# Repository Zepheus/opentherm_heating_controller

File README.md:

# Andiron

**ESP32-C6 heating controller for a UK wiring centre, built for Home Assistant and ESPHome.**
Board revision v1.0

Andiron is an isolated I/O board for a domestic heating system. It sits in the
wiring centre, switches the zone valves and boiler demand through four
volt-free changeover relays, and talks to the boiler over OpenTherm. All the logic (schedules, thermostats, weather compensation) lives
in Home Assistant. The board was designed around an ESPHome firmware, which
will be written and published once the first boards are in hand.

| | |
|---|---|
| MCU | ESP32-C6-WROOM-1 (WiFi 6, BLE), USB-C power and programming |
| Boiler | OpenTherm master (opto-isolated, fused against a 230 V miswire) |
| Outputs | 4 × volt-free changeover relays (CH1–CH4), NC / COM / NO terminals, 250 VAC 3 A, each channel isolated from the others |
| Sensors | 2 × 1-Wire probe terminals (flow, outdoor), 2 × Qwiic I²C (one for the OLED, on a cable), 8-pin spare GPIO header |
| Board | 160 × 95 mm, 2 layers, wall-hanging with all cables from below or the left, 6.4 mm isolation around every relay channel, JLCPCB assembly |

> **Mains voltage.** The relay contacts can switch 230 V. Do not build or
> install it unless you are competent to work on mains wiring, and read the
> safety notes in [`docs/design.md`](docs/design.md) first. Status: v1.0 passes
> ERC, DRC and the spacing checks, but no board has been built or tested yet.

## Renders

| Top | Bottom |
|---|---|
|  |  |
|  |  |

The 3D views use stand-in models for the ESP32-C6 module (ESP32-S3-WROOM-1,
same body) and the USB-C receptacle (GCT USB4105, same footprint).

## Bill of materials

The full BOM with LCSC part numbers and cost estimates is in
[`docs/BOM.md`](docs/BOM.md); the JLCPCB upload file is
[`docs/bom/andiron-bom-jlc.csv`](docs/bom/andiron-bom-jlc.csv). At LCSC prices
from October 2026, components came to roughly $16 per board, or about $24 per
board for a run of five once Extended-part loading fees are included. The four
relays are $7.60 of that. PCB,
assembly and shipping come on top, from the JLCPCB quote.

## Getting started

### Tools

| Tool | Used for |
|---|---|
| [KiCad 10](https://www.kicad.org/) | schematic, layout, DRC, renders (`kicad-cli`) |
| [Konnect](https://github.com/mixelpixx/Konnect) MCP server (0.13, KiCad 10 plugin) | lets Claude Code read and edit the KiCad project, search the JLCPCB parts database |
| [Freerouting](https://github.com/freerouting/freerouting) 2.x + Java | autorouting |
| [easyeda2kicad](https://github.com/uPesy/easyeda2kicad.py) | importing JLC/LCSC symbols, footprints and 3D models into `lib/` |
| Python 3 | the scripts in `tools/` |

### Working on the board with Claude Code and Konnect

1. Install KiCad 10 and Konnect, and put `konnect` on your `PATH` (or point
   [`.mcp.json`](.mcp.json) at it).
2. Open the repository in Claude Code and approve the Konnect server when
   asked. Claude can then read and edit the schematic and board, run ERC and
   DRC, and search JLCPCB parts.
3. Ask Konnect to download the JLCPCB parts database once
   (`download_jlcpcb_database`); `tools/bom.py` reads the same file for prices.
4. Start with [`docs/requirements.md`](docs/requirements.md) and
   [`docs/design.md`](docs/design.md) for what the board does and why.

The layout is generated, not drawn by hand: part positions live in
`tools/layout/place.py`, shared dimensions (relay row, terminals, isolation
zones, slots, antenna keep-out) in `tools/layout/geometry.py`, and hand-laid
copper in `tools/route/prep_board.py`. Edit those and rerun the pipeline rather
than moving tracks in the PCB editor.

### Regenerating outputs

```sh
KPY=/Applications/KiCad/KiCad.app/Contents/Frameworks/Python.framework/Versions/Current/bin/python3
$KPY -I tools/sync_netlist.py "$PWD" tools/route/placed.kicad_pcb   # after a schematic change
$KPY -I tools/layout/place.py tools/route/placed.kicad_pcb          # after a placement change
tools/route/run_pipeline.sh "$PWD" 40    # route, pour, silkscreen, DRC, sanity (close the PCB editor first)
python3 tools/bom.py                     # docs/BOM.md and docs/bom/andiron-bom-jlc.csv
tools/render.sh                          # docs/images/
```

## Repository layout

| Path | What |
|---|---|
| `heating-controller.kicad_pro` / `.kicad_sch` / `.kicad_pcb` | KiCad 10 project (root sheet plus `power_mcu`, `opentherm`, `relays`) |
| `heating-controller.kicad_dru` | custom DRC rules: mains isolation, clearances, track widths |
| `.konnect/project.json` | design rules in prose, read by Konnect during layout |
| `lib/` | project symbols, footprints and 3D models (from JLC/EasyEDA) |
| `docs/requirements.md` | numbered requirements (what) |
| `docs/design.md` | decisions, safety framing, GPIO map, layout, open questions (why) |
| `docs/layout-notes.md` | what worked and what did not in placement and routing |
| `docs/BOM.md`, `docs/bom/` | bill of materials and JLCPCB upload file |
| `tools/` | routing pipeline, BOM, renders, 3D model sync, checks; see [`tools/README.md`](tools/README.md) |

Open questions that must be answered before ordering are at the end of
[`docs/design.md`](docs/design.md); the boiler model code is the main one.

## License

Open hardware. The board design and documentation are licensed under the
[CERN Open Hardware Licence v2, Permissive](LICENSES/CERN-OHL-P-2.0.txt), the
hardware counterpart of MIT; the scripts in `tools/` are under the
[MIT License](LICENSES/MIT.txt). See [`LICENSE`](LICENSE).

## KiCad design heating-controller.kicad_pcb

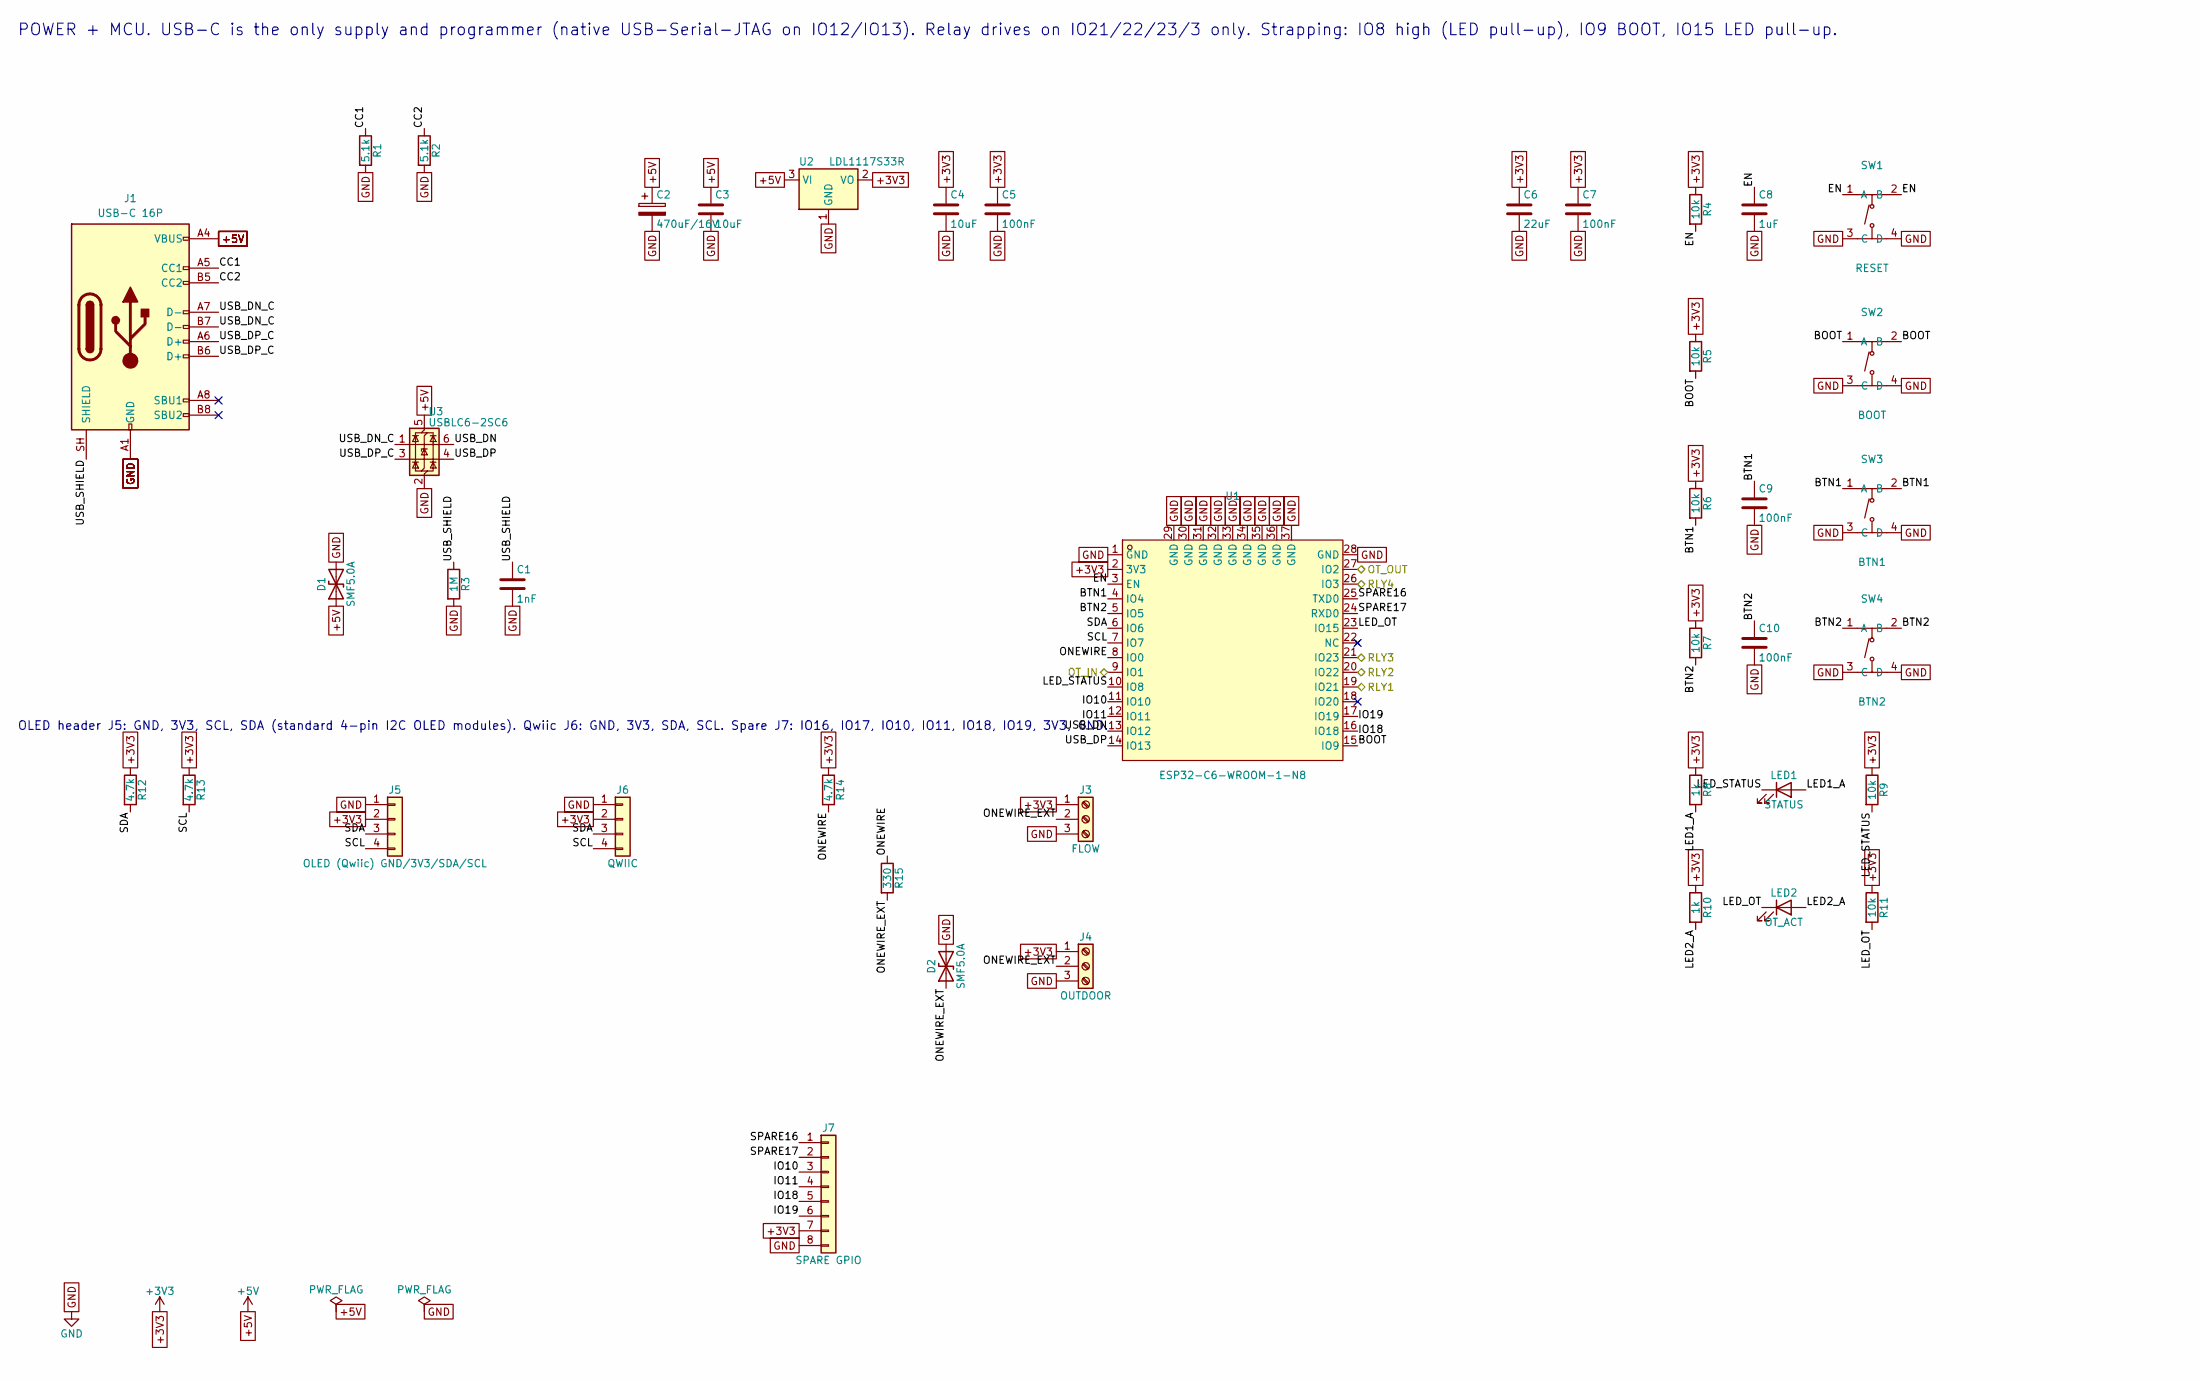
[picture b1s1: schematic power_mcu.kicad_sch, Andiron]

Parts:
C1: 1nF; C_0603_1608Metric; LCSC C1588
C2: 470uF/16V; CP_Elec_8x10; LCSC C3341
C3, C4: 10uF; C_0805_2012Metric; LCSC C15850
C5, C7, C9, C10: 100nF; C_0603_1608Metric; LCSC C14663
C6: 22uF; C_0805_2012Metric; LCSC C45783
C8: 1uF; C_0603_1608Metric; LCSC C15849
D1, D2: SMF5.0A; D_SOD-123F; LCSC C19077497
J1: USB-C 16P; USB_C_Receptacle_HRO_TYPE-C-31-M-12; LCSC C165948
J3: FLOW; CONN-TH_3P-P3.50_KF350-3.5-3P; LCSC C474893
J4: OUTDOOR; CONN-TH_3P-P3.50_KF350-3.5-3P; LCSC C474893
J5: OLED (Qwiic) GND/3V3/SDA/SCL; JST_SH_SM04B-SRSS-TB_1x04-1MP_P1.00mm_Horizontal; LCSC C160404
J6: QWIIC; JST_SH_SM04B-SRSS-TB_1x04-1MP_P1.00mm_Horizontal; LCSC C160404
J7: SPARE GPIO; PinHeader_1x08_P2.54mm_Vertical; LCSC C492407
LED1: STATUS; LED_0603_1608Metric; LCSC C2286
LED2: OT_ACT; LED_0603_1608Metric; LCSC C2286
R1, R2: 5.1k; R_0603_1608Metric; LCSC C23186
R3: 1M; R_0603_1608Metric; LCSC C22935
R4, R5, R6, R7, R9, R11: 10k; R_0603_1608Metric; LCSC C25804
R8, R10: 1k; R_0603_1608Metric; LCSC C21190
R12, R13, R14: 4.7k; R_0603_1608Metric; LCSC C23162
R15: 330; R_0603_1608Metric; LCSC C23138
SW1: RESET; SW-SMD_4P-L5.1-W5.1-P3.70-LS6.5-TL_H1.5; LCSC C318884
SW2: BOOT; SW-SMD_4P-L5.1-W5.1-P3.70-LS6.5-TL_H1.5; LCSC C318884
SW3: BTN1; SW-SMD_4P-L5.1-W5.1-P3.70-LS6.5-TL_H1.5; LCSC C318884
SW4: BTN2; SW-SMD_4P-L5.1-W5.1-P3.70-LS6.5-TL_H1.5; LCSC C318884
U1: ESP32-C6-WROOM-1-N8; WIRELM-SMD_ESP32-C6-WROOM-1; LCSC C5366877
U2: LDL1117S33R; SOT-223-3_TabPin2; LCSC C435835
U3: USBLC6-2SC6; SOT-23-6; LCSC C7519

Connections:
+3V3: C4.1, C5.1, C6.1, C7.1, J3.1, J4.1, J5.2, J6.2, J7.7, R4.1, R5.1, R6.1, R7.1, R8.1, R9.1, R10.1, R11.1, R12.1, R13.1, R14.1, U1.2 (3V3), U2.2 (VO); also elsewhere on the board
/OT_IN: U1.9 (IO1); also elsewhere on the board
/OT_OUT: U1.27 (IO2); also elsewhere on the board
/Power + MCU/BOOT: R5.2, SW2.1 (A), SW2.2 (B), U1.15 (IO9)
/Power + MCU/BTN1: C9.1, R6.2, SW3.1 (A), SW3.2 (B), U1.4 (IO4)
/Power + MCU/BTN2: C10.1, R7.2, SW4.1 (A), SW4.2 (B), U1.5 (IO5)
/Power + MCU/CC1: J1.A5 (CC1), R1.1
/Power + MCU/CC2: J1.B5 (CC2), R2.1
/Power + MCU/EN: C8.1, R4.2, SW1.1 (A), SW1.2 (B), U1.3 (EN)
/Power + MCU/IO10: J7.3, U1.11 (IO10)
/Power + MCU/IO11: J7.4, U1.12 (IO11)
/Power + MCU/IO18: J7.5, U1.16 (IO18)
/Power + MCU/IO19: J7.6, U1.17 (IO19)
/Power + MCU/LED1_A: LED1.2 (A), R8.2
/Power + MCU/LED2_A: LED2.2 (A), R10.2
/Power + MCU/LED_OT: LED2.1 (K), R11.2, U1.23 (IO15)
/Power + MCU/LED_STATUS: LED1.1 (K), R9.2, U1.10 (IO8)
/Power + MCU/ONEWIRE: R14.2, R15.1, U1.8 (IO0)
/Power + MCU/ONEWIRE_EXT: D2.1 (A1), J3.2, J4.2, R15.2
/Power + MCU/SCL: J5.4, J6.4, R13.2, U1.7 (IO7)
/Power + MCU/SDA: J5.3, J6.3, R12.2, U1.6 (IO6)
/Power + MCU/SPARE16: J7.1, U1.25 (TXD0)
/Power + MCU/SPARE17: J7.2, U1.24 (RXD0)
/Power + MCU/USB_DN: U1.13 (IO12), U3.6 (I/O1)
/Power + MCU/USB_DN_C: J1.A7 (D-), J1.B7 (D-), U3.1 (I/O1)
/Power + MCU/USB_DP: U1.14 (IO13), U3.4 (I/O2)
/Power + MCU/USB_DP_C: J1.A6 (D+), J1.B6 (D+), U3.3 (I/O2)
/Power + MCU/USB_SHIELD: C1.1, J1.SH (SHIELD), R3.1
/RLY1: U1.19 (IO21); also elsewhere on the board
/RLY2: U1.20 (IO22); also elsewhere on the board
/RLY3: U1.21 (IO23); also elsewhere on the board
/RLY4: U1.26 (IO3); also elsewhere on the board

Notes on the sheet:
POWER + MCU. USB-C is the only supply and programmer (native USB-Serial-JTAG on IO12/IO13). Relay drives on IO21/22/23/3 only. Strapping: IO8 high (LED pull-up), IO9 BOOT, IO15 LED pull-up.
OLED header J5: GND, 3V3, SCL, SDA (standard 4-pin I2C OLED modules). Qwiic J6: GND, 3V3, SDA, SCL. Spare J7: IO16, IO17, IO10, IO11, IO18, IO19, 3V3, GND.

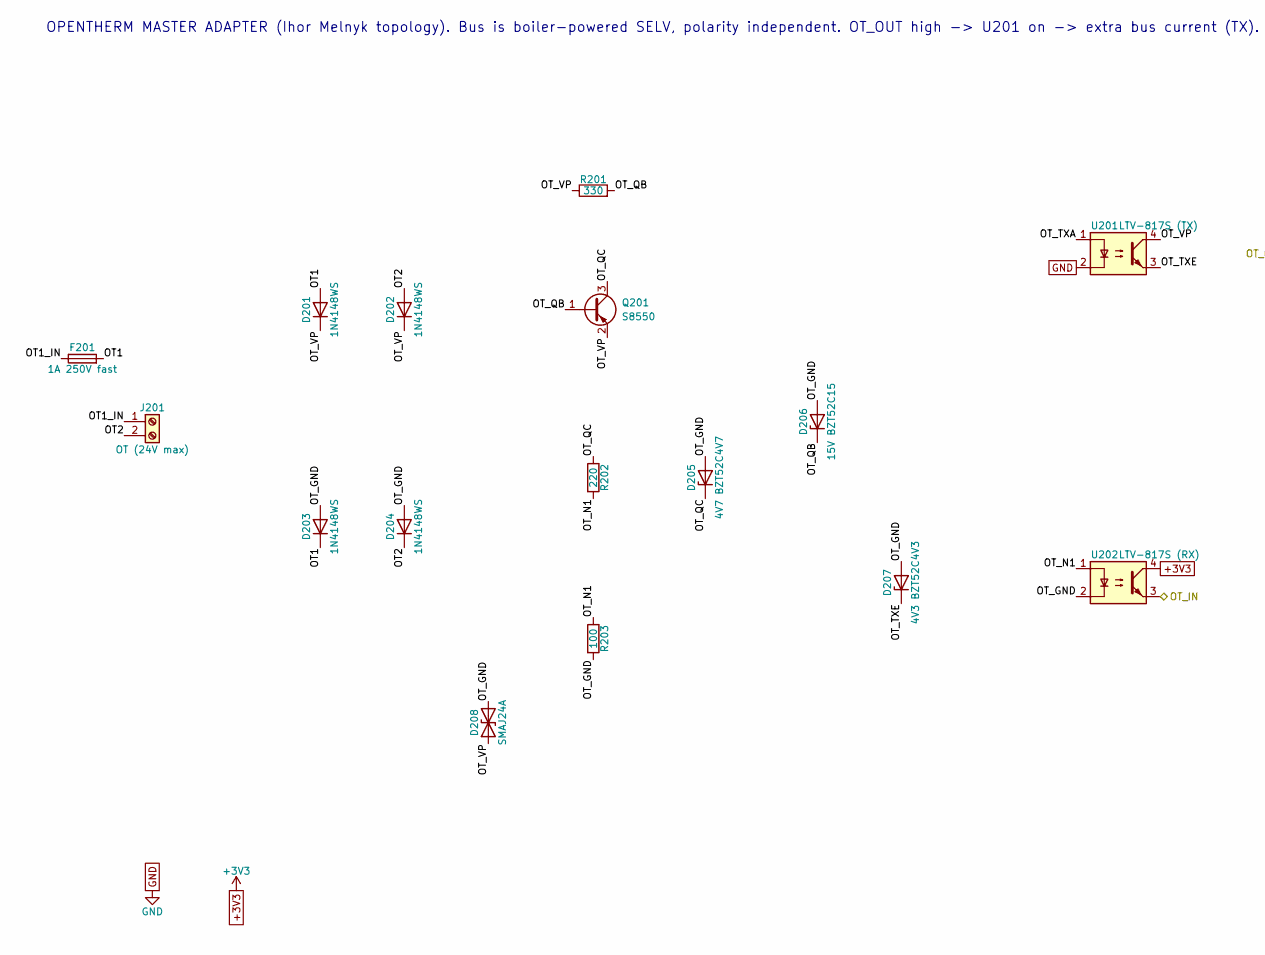
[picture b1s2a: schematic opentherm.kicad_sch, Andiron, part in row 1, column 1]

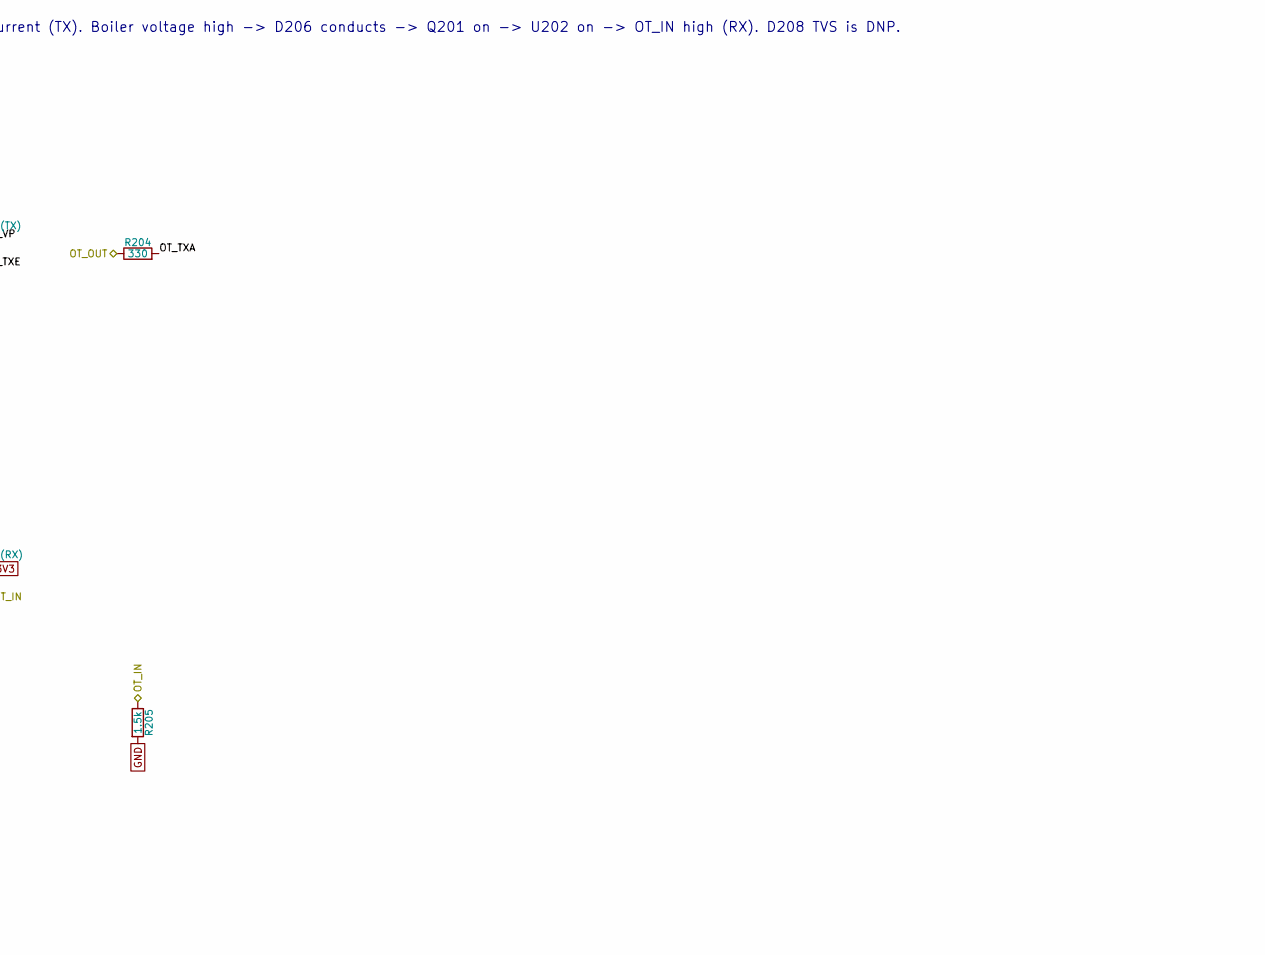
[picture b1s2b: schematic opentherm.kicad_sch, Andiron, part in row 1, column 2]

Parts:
D201, D202, D203, D204: 1N4148WS; D_SOD-323; LCSC C2128
D205: 4V7 BZT52C4V7; D_SOD-123; LCSC C19077400
D206: 15V BZT52C15; D_SOD-123; LCSC C19077412
D207: 4V3 BZT52C4V3; D_SOD-123; LCSC C19077399
D208: SMAJ24A; D_SMA; LCSC C19077541
F201: 1A 250V fast; Fuse_Littelfuse-NANO2-451_453; LCSC C83798
J201: OT (24V max); CONN-TH_P3.50_KF350-3.5-2P; LCSC C474892
Q201: S8550; SOT-23; LCSC C105432
R201: 330; R_1206_3216Metric; LCSC C17930
R202: 220; R_0603_1608Metric; LCSC C22962
R203: 100; R_0603_1608Metric; LCSC C22775
R204: 330; R_0603_1608Metric; LCSC C23138
R205: 1.5k; R_0603_1608Metric; LCSC C22843
U201: LTV-817S (TX); OPTO-SMD-4_L4.6-W6.5-P2.54-LS10.3-BL; LCSC C109227
U202: LTV-817S (RX); OPTO-SMD-4_L4.6-W6.5-P2.54-LS10.3-BL; LCSC C109227

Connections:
+3V3: U202.4; also elsewhere on the board
/OT_IN: R205.1, U202.3; also elsewhere on the board
/OT_OUT: R204.1; also elsewhere on the board
/OpenTherm/OT1: D201.2 (A), D203.1 (K), F201.2
/OpenTherm/OT1_IN: F201.1, J201.1
/OpenTherm/OT2: D202.2 (A), D204.1 (K), J201.2
/OpenTherm/OT_GND: D203.2 (A), D204.2 (A), D205.2 (A), D206.2 (A), D207.2 (A), D208.2 (A2), R203.2, U202.2
/OpenTherm/OT_N1: R202.2, R203.1, U202.1
/OpenTherm/OT_QB: D206.1 (K), Q201.1 (B), R201.2
/OpenTherm/OT_QC: D205.1 (K), Q201.3 (C), R202.1
/OpenTherm/OT_TXA: R204.2, U201.1
/OpenTherm/OT_TXE: D207.1 (K), U201.3
/OpenTherm/OT_VP: D201.1 (K), D202.1 (K), D208.1 (A1), Q201.2 (E), R201.1, U201.4

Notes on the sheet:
OPENTHERM MASTER ADAPTER (Ihor Melnyk topology). Bus is boiler-powered SELV, polarity independent. OT_OUT high -> U201 on -> extra bus current (TX). Boiler voltage high -> D206 conducts -> Q201 on -> U202 on -> OT_IN high (RX). D208 TVS is DNP.

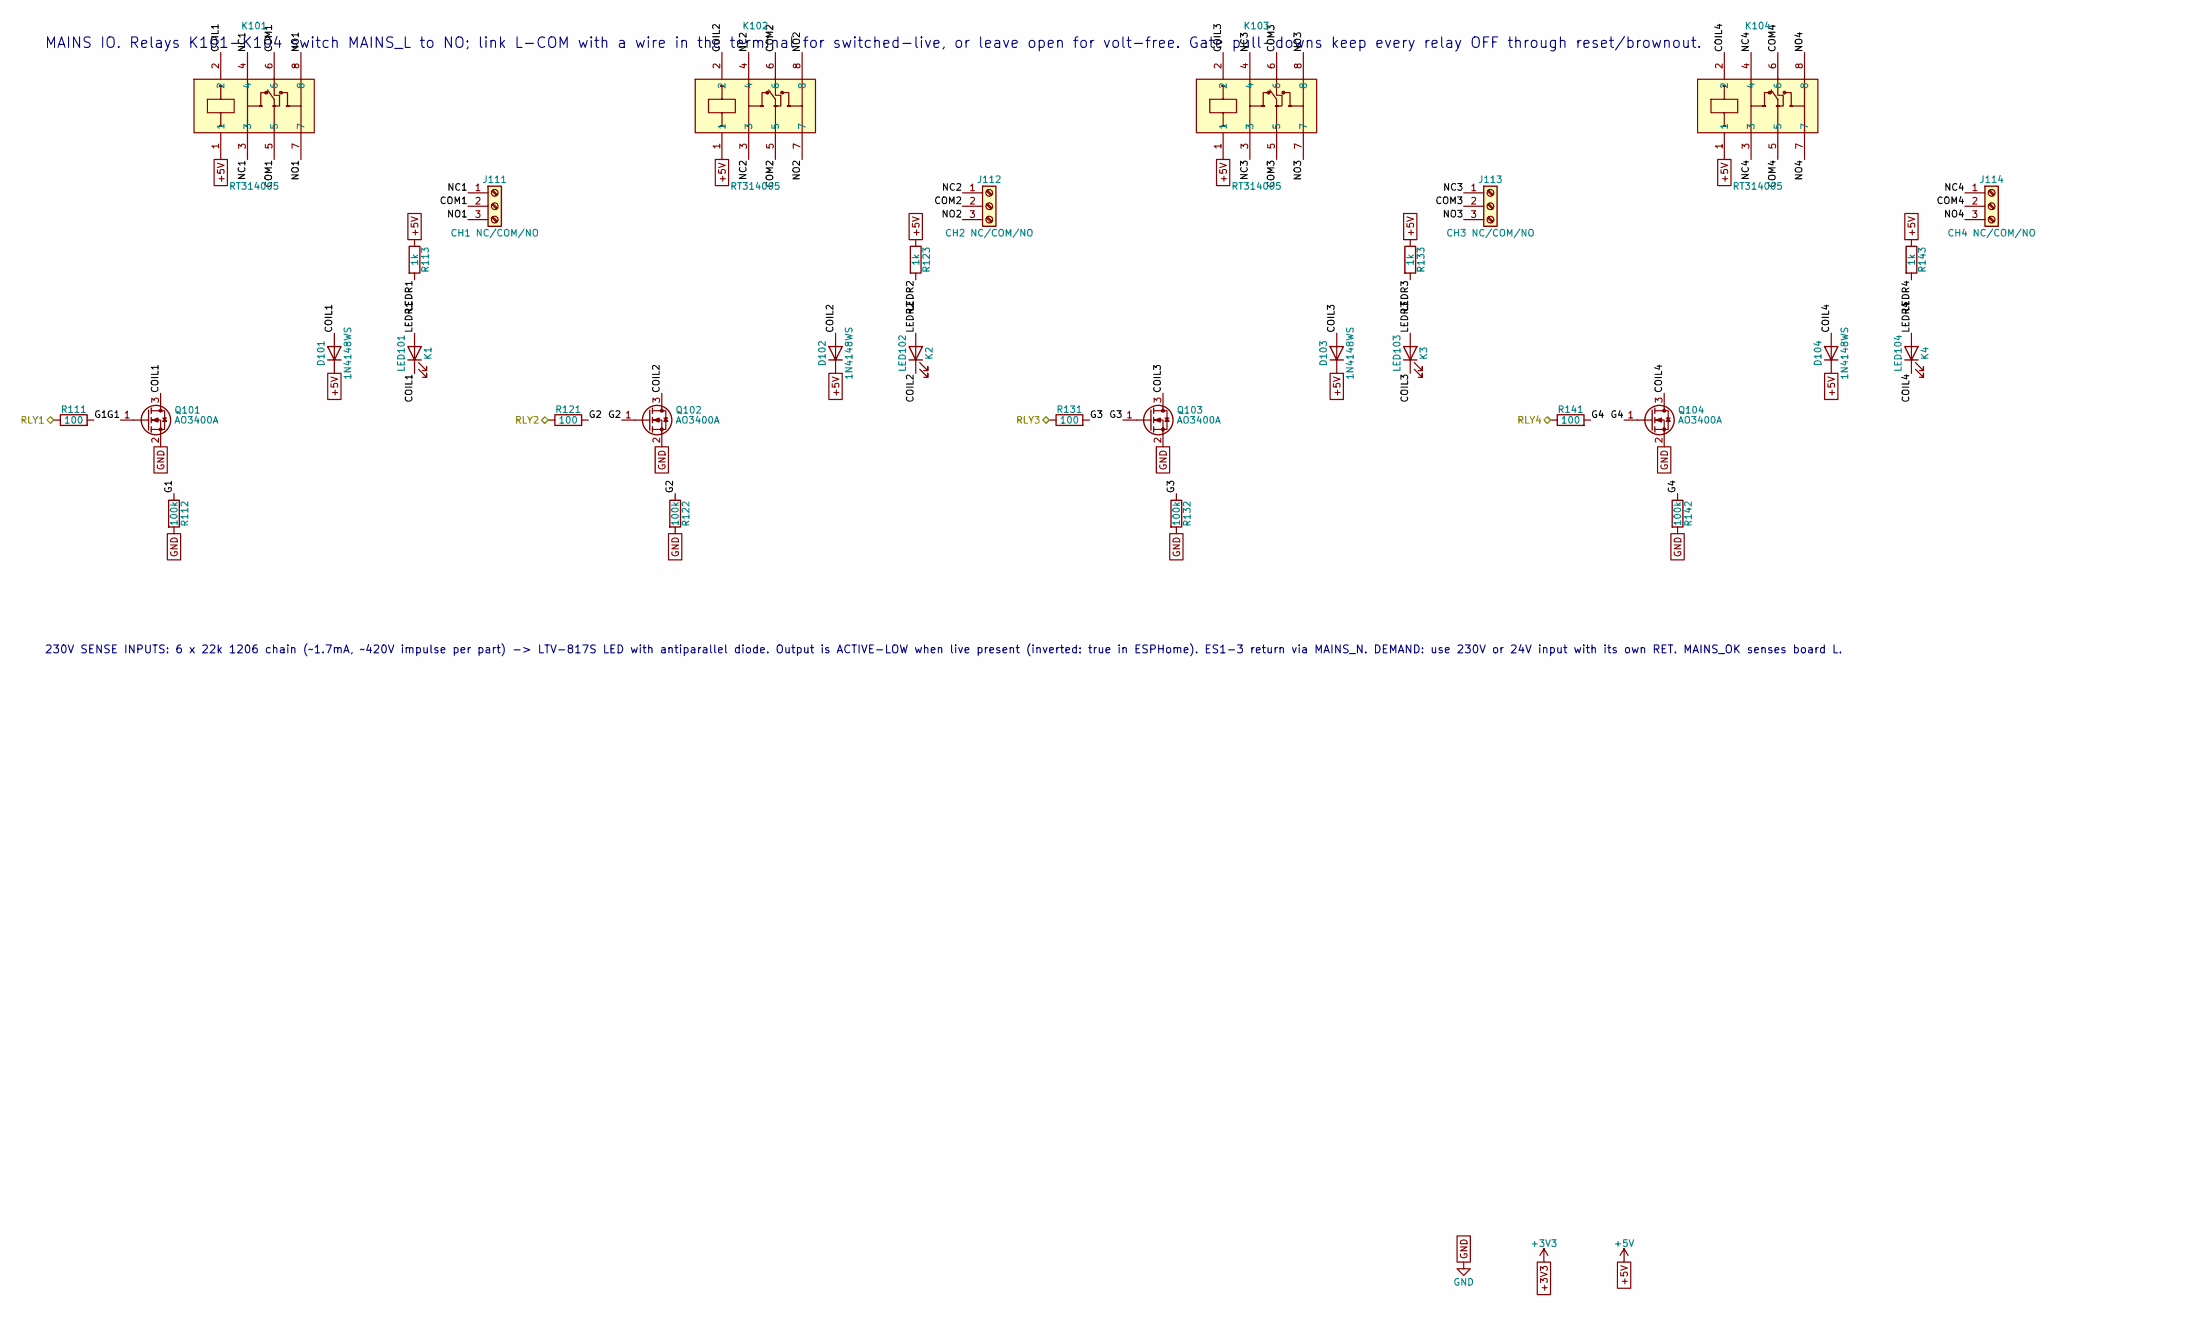
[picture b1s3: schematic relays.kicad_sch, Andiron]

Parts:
D101, D102, D103, D104: 1N4148WS; D_SOD-323; LCSC C2128
J111: CH1 NC/COM/NO; CONN-TH_3P-P5.00_WJ128V-5.0-3P; LCSC C8270
J112: CH2 NC/COM/NO; CONN-TH_3P-P5.00_WJ128V-5.0-3P; LCSC C8270
J113: CH3 NC/COM/NO; CONN-TH_3P-P5.00_WJ128V-5.0-3P; LCSC C8270
J114: CH4 NC/COM/NO; CONN-TH_3P-P5.00_WJ128V-5.0-3P; LCSC C8270
K101, K102, K103, K104: RT314005; RELAY-TH_RT314005_HF115F-PINS; LCSC C7065270
LED101: K1; LED_0603_1608Metric; LCSC C2286
LED102: K2; LED_0603_1608Metric; LCSC C2286
LED103: K3; LED_0603_1608Metric; LCSC C2286
LED104: K4; LED_0603_1608Metric; LCSC C2286
Q101, Q102, Q103, Q104: AO3400A; SOT-23; LCSC C20917
R111, R121, R131, R141: 100; R_0603_1608Metric; LCSC C22775
R112, R122, R132, R142: 100k; R_0603_1608Metric; LCSC C25803
R113, R123, R133, R143: 1k; R_0603_1608Metric; LCSC C21190

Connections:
/RLY1: R111.1; also elsewhere on the board
/RLY2: R121.1; also elsewhere on the board
/RLY3: R131.1; also elsewhere on the board
/RLY4: R141.1; also elsewhere on the board
/Relays/COIL1: D101.2 (A), K101.2, LED101.1 (K), Q101.3 (D)
/Relays/COIL2: D102.2 (A), K102.2, LED102.1 (K), Q102.3 (D)
/Relays/COIL3: D103.2 (A), K103.2, LED103.1 (K), Q103.3 (D)
/Relays/COIL4: D104.2 (A), K104.2, LED104.1 (K), Q104.3 (D)
/Relays/COM1: J111.2, K101.5, K101.6
/Relays/COM2: J112.2, K102.5, K102.6
/Relays/COM3: J113.2, K103.5, K103.6
/Relays/COM4: J114.2, K104.5, K104.6
/Relays/G1: Q101.1 (G), R111.2, R112.1
/Relays/G2: Q102.1 (G), R121.2, R122.1
/Relays/G3: Q103.1 (G), R131.2, R132.1
/Relays/G4: Q104.1 (G), R141.2, R142.1
/Relays/LEDR1: LED101.2 (A), R113.2
/Relays/LEDR2: LED102.2 (A), R123.2
/Relays/LEDR3: LED103.2 (A), R133.2
/Relays/LEDR4: LED104.2 (A), R143.2
/Relays/NC1: J111.1, K101.3, K101.4
/Relays/NC2: J112.1, K102.3, K102.4
/Relays/NC3: J113.1, K103.3, K103.4
/Relays/NC4: J114.1, K104.3, K104.4
/Relays/NO1: J111.3, K101.7, K101.8
/Relays/NO2: J112.3, K102.7, K102.8
/Relays/NO3: J113.3, K103.7, K103.8
/Relays/NO4: J114.3, K104.7, K104.8

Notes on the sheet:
MAINS IO. Relays K101-K104 switch MAINS_L to NO; link L-COM with a wire in the terminal for switched-live, or leave open for volt-free. Gate pull-downs keep every relay OFF through reset/brownout.
230V SENSE INPUTS: 6 x 22k 1206 chain (~1.7mA, ~420V impulse per part) -> LTV-817S LED with antiparallel diode. Output is ACTIVE-LOW when live present (inverted: true in ESPHome). ES1-3 return via MAINS_N. DEMAND: use 230V or 24V input with its own RET. MAINS_OK senses board L.

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
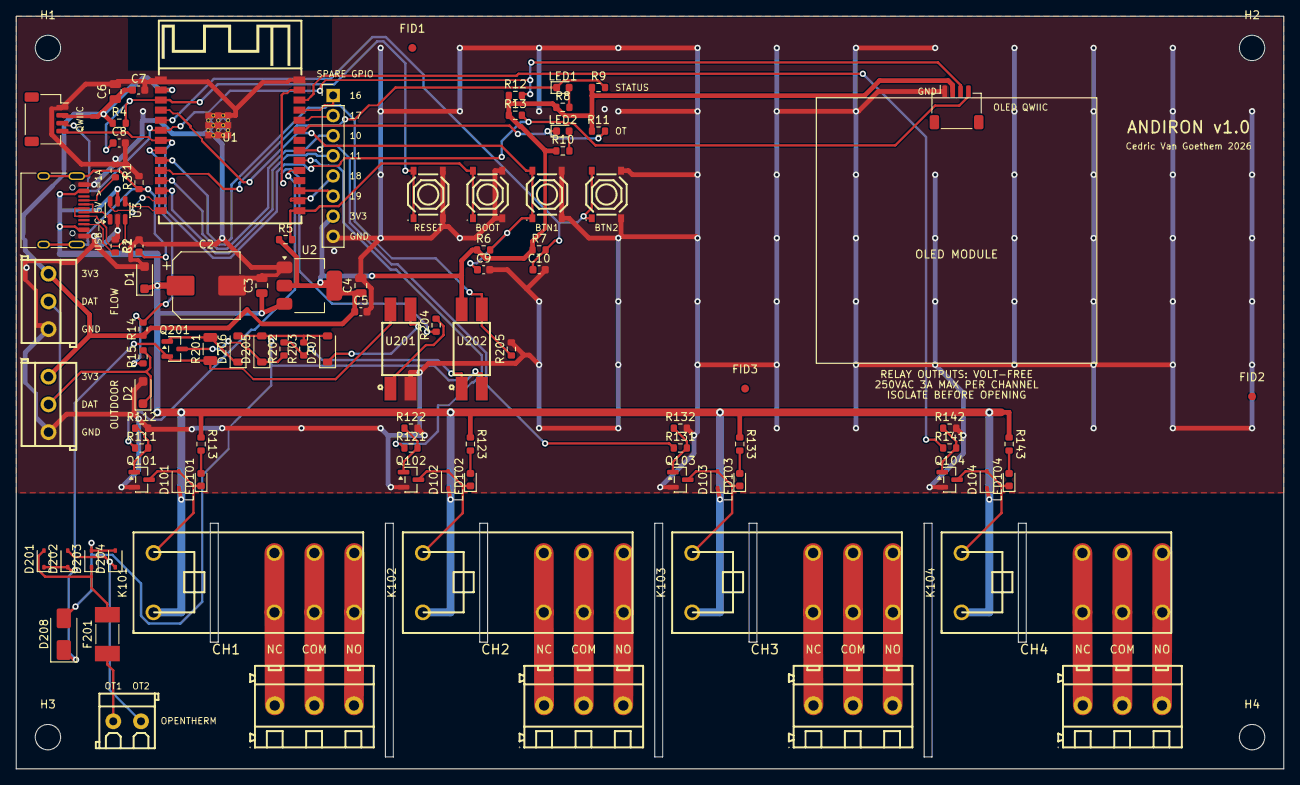
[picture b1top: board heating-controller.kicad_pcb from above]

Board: 2 copper layers, 160.0 x 95.0 mm, 99 parts (0 on the bottom side), 68 nets.

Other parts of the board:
FID1, FID2, FID3: Fiducial_1mm_Mask3mm
H1, H2, H3, H4: MountingHole_3.2mm_M3

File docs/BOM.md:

# Andiron v1.0 — bill of materials

Generated by `tools/bom.py` from the schematic on 2026-10-22. Prices: LCSC single-unit prices from the JLCPCB parts database snapshot of 2026-10-20; they are estimates, not a quote. Upload file for JLCPCB assembly: [`bom/andiron-bom-jlc.csv`](bom/andiron-bom-jlc.csv) (fitted parts only; the placement file comes from the board).

## Cost summary

| Item | USD |
|---|---:|
| Components per board (92 placements, 39 unique parts) | 15.96 |
| Extended-part loading fees per order (13 × $3.00, assumed) | 39.00 |
| **Components per board at 5 boards, fees included** | **23.76** |

PCB fabrication, assembly setup, through-hole soldering, stencil and shipping are not included; take them from the JLCPCB quote. The Library column is what the parts database reports; "Preferred" parts carry no loading fee on Economic assembly, so only "Extended" parts are counted. Swapping an Extended part for a Basic or Preferred equivalent saves its fee.

## Fitted parts

| Qty | References | Value | Footprint | LCSC | Manufacturer part | Library | Unit | Line |
|---:|---|---|---|---|---|---|---:|---:|
| 1 | C1 | 1nF | C_0603_1608Metric | [C1588](https://jlcpcb.com/partdetail/C1588) | Samsung Electro-Mechanics CL10B102KB8NNNC | Basic | 0.0090 | 0.01 |
| 1 | C2 | 470uF/16V | CP_Elec_8x10 | [C3341](https://jlcpcb.com/partdetail/C3341) | Honor Elec RVT1C471M0810 | Extended | 0.0650 | 0.07 |
| 2 | C3, C4 | 10uF | C_0805_2012Metric | [C15850](https://jlcpcb.com/partdetail/C15850) | Samsung Electro-Mechanics CL21A106KAYNNNE | Basic | 0.0440 | 0.09 |
| 4 | C5, C7, C9, C10 | 100nF | C_0603_1608Metric | [C14663](https://jlcpcb.com/partdetail/C14663) | YAGEO CC0603KRX7R9BB104 | Basic | 0.0110 | 0.04 |
| 1 | C6 | 22uF | C_0805_2012Metric | [C45783](https://jlcpcb.com/partdetail/C45783) | Samsung Electro-Mechanics CL21A226MAQNNNE | Basic | 0.1940 | 0.19 |
| 1 | C8 | 1uF | C_0603_1608Metric | [C15849](https://jlcpcb.com/partdetail/C15849) | Samsung Electro-Mechanics CL10A105KB8NNNC | Basic | 0.0140 | 0.01 |
| 2 | D1, D2 | SMF5.0A | D_SOD-123F | [C19077497](https://jlcpcb.com/partdetail/C19077497) | hongjiacheng SMF5.0A | Preferred | 0.0280 | 0.06 |
| 8 | D101, D102, D103, D104, D201, D202, D203, D204 | 1N4148WS | D_SOD-323 | [C2128](https://jlcpcb.com/partdetail/C2128) | Jiangsu Changjing Electronics Technology Co., Ltd. 1N4148WS | Basic | 0.0150 | 0.12 |
| 1 | D205 | 4V7 BZT52C4V7 | D_SOD-123 | [C19077400](https://jlcpcb.com/partdetail/C19077400) | hongjiacheng BZT52C4V7 | Preferred | 0.0120 | 0.01 |
| 1 | D206 | 15V BZT52C15 | D_SOD-123 | [C19077412](https://jlcpcb.com/partdetail/C19077412) | hongjiacheng BZT52C15 | Preferred | 0.0180 | 0.02 |
| 1 | D207 | 4V3 BZT52C4V3 | D_SOD-123 | [C19077399](https://jlcpcb.com/partdetail/C19077399) | hongjiacheng BZT52C4V3 | Preferred | 0.0180 | 0.02 |
| 1 | D208 | SMAJ24A | D_SMA | [C19077541](https://jlcpcb.com/partdetail/C19077541) | hongjiacheng SMAJ24A | Preferred | 0.0380 | 0.04 |
| 1 | F201 | 1A 250V fast | Fuse_Littelfuse-NANO2-451_453 | [C83798](https://jlcpcb.com/partdetail/C83798) | AEM MF2410F1.000TM | Extended | 0.0930 | 0.09 |
| 1 | J1 | USB-C 16P | USB_C_Receptacle_HRO_TYPE-C-31-M-12 | [C165948](https://jlcpcb.com/partdetail/C165948) | Korean Hroparts Elec TYPE-C-31-M-12 | Extended | 0.1860 | 0.19 |
| 2 | J3, J4 | FLOW / OUTDOOR | CONN-TH_3P-P3.50_KF350-3.5-3P | [C474893](https://jlcpcb.com/partdetail/C474893) | Cixi Kefa Elec KF350-3.5-3P | Extended | 0.1550 | 0.31 |
| 2 | J5, J6 | OLED (Qwiic) GND/3V3/SDA/SCL / QWIIC | JST_SH_SM04B-SRSS-TB_1x04-1MP_P1.00mm_Horizontal | [C160404](https://jlcpcb.com/partdetail/C160404) | JST SM04B-SRSS-TB(LF)(SN) | Extended | 0.2140 | 0.43 |
| 1 | J7 | SPARE GPIO | PinHeader_1x08_P2.54mm_Vertical | [C492407](https://jlcpcb.com/partdetail/C492407) | XFCN PZ254V-11-08P | Extended | 0.0520 | 0.05 |
| 4 | J111, J112, J113, J114 | CH1 NC/COM/NO / CH2 NC/COM/NO / CH3 NC/COM/NO / CH4 NC/COM/NO | CONN-TH_3P-P5.00_WJ128V-5.0-3P | [C8270](https://jlcpcb.com/partdetail/C8270) | Ningbo Kangnex Elec WJ128V-5.0-03P-14-00A | Extended | 0.2090 | 0.84 |
| 1 | J201 | OT (24V max) | CONN-TH_P3.50_KF350-3.5-2P | [C474892](https://jlcpcb.com/partdetail/C474892) | Cixi Kefa Elec KF350-3.5-2P | Extended | 0.1190 | 0.12 |
| 4 | K101, K102, K103, K104 | RT314005 | RELAY-TH_RT314005_HF115F-PINS | [C7065270](https://jlcpcb.com/partdetail/C7065270) | TE Connectivity RT314005 | Extended | 1.8920 | 7.57 |
| 6 | LED1, LED2, LED101, LED102, LED103, LED104 | STATUS / OT_ACT / K1 / K2 / K3 / K4 | LED_0603_1608Metric | [C2286](https://jlcpcb.com/partdetail/C2286) | Hubei KENTO Elec KT-0603R | Basic | 0.0080 | 0.05 |
| 4 | Q101, Q102, Q103, Q104 | AO3400A | SOT-23 | [C20917](https://jlcpcb.com/partdetail/C20917) | Alpha & Omega Semicon AO3400A | Basic | 0.0970 | 0.39 |
| 1 | Q201 | S8550 | SOT-23 | [C105432](https://jlcpcb.com/partdetail/C105432) | Jiangsu Changjing Electronics Technology Co., Ltd. S8550(RANGE:120-200) | Basic | 0.0170 | 0.02 |
| 2 | R1, R2 | 5.1k | R_0603_1608Metric | [C23186](https://jlcpcb.com/partdetail/C23186) | UNI-ROYAL(Uniroyal Elec) 0603WAF5101T5E | Basic | 0.0020 | 0.00 |
| 1 | R3 | 1M | R_0603_1608Metric | [C22935](https://jlcpcb.com/partdetail/C22935) | UNI-ROYAL(Uniroyal Elec) 0603WAF1004T5E | Basic | 0.0020 | 0.00 |
| 6 | R4, R5, R6, R7, R9, R11 | 10k | R_0603_1608Metric | [C25804](https://jlcpcb.com/partdetail/C25804) | UNI-ROYAL(Uniroyal Elec) 0603WAF1002T5E | Basic | 0.0020 | 0.01 |
| 6 | R8, R10, R113, R123, R133, R143 | 1k | R_0603_1608Metric | [C21190](https://jlcpcb.com/partdetail/C21190) | UNI-ROYAL(Uniroyal Elec) 0603WAF1001T5E | Basic | 0.0030 | 0.02 |
| 3 | R12, R13, R14 | 4.7k | R_0603_1608Metric | [C23162](https://jlcpcb.com/partdetail/C23162) | UNI-ROYAL(Uniroyal Elec) 0603WAF4701T5E | Basic | 0.0030 | 0.01 |
| 2 | R15, R204 | 330 | R_0603_1608Metric | [C23138](https://jlcpcb.com/partdetail/C23138) | UNI-ROYAL(Uniroyal Elec) 0603WAF3300T5E | Basic | 0.0020 | 0.00 |
| 5 | R111, R121, R131, R141, R203 | 100 | R_0603_1608Metric | [C22775](https://jlcpcb.com/partdetail/C22775) | UNI-ROYAL(Uniroyal Elec) 0603WAF1000T5E | Basic | 0.0030 | 0.01 |
| 4 | R112, R122, R132, R142 | 100k | R_0603_1608Metric | [C25803](https://jlcpcb.com/partdetail/C25803) | UNI-ROYAL(Uniroyal Elec) 0603WAF1003T5E | Basic | 0.0030 | 0.01 |
| 1 | R201 | 330 | R_1206_3216Metric | [C17930](https://jlcpcb.com/partdetail/C17930) | UNI-ROYAL(Uniroyal Elec) 1206W4F3300T5E | Extended | 0.0050 | 0.01 |
| 1 | R202 | 220 | R_0603_1608Metric | [C22962](https://jlcpcb.com/partdetail/C22962) | UNI-ROYAL(Uniroyal Elec) 0603WAF2200T5E | Basic | 0.0030 | 0.00 |
| 1 | R205 | 1.5k | R_0603_1608Metric | [C22843](https://jlcpcb.com/partdetail/C22843) | UNI-ROYAL(Uniroyal Elec) 0603WAF1501T5E | Basic | 0.0020 | 0.00 |
| 4 | SW1, SW2, SW3, SW4 | RESET / BOOT / BTN1 / BTN2 | SW-SMD_4P-L5.1-W5.1-P3.70-LS6.5-TL_H1.5 | [C318884](https://jlcpcb.com/partdetail/C318884) | XKB Connection TS-1187A-B-A-B | Basic | 0.0210 | 0.08 |
| 1 | U1 | ESP32-C6-WROOM-1-N8 | WIRELM-SMD_ESP32-C6-WROOM-1 | [C5366877](https://jlcpcb.com/partdetail/C5366877) | Espressif Systems ESP32-C6-WROOM-1-N8 | Extended | 4.2330 | 4.23 |
| 1 | U2 | LDL1117S33R | SOT-223-3_TabPin2 | [C435835](https://jlcpcb.com/partdetail/C435835) | STMicroelectronics LDL1117S33R | Extended | 0.5010 | 0.50 |
| 1 | U3 | USBLC6-2SC6 | SOT-23-6 | [C7519](https://jlcpcb.com/partdetail/C7519) | STMicroelectronics USBLC6-2SC6 | Extended | 0.1770 | 0.18 |
| 2 | U201, U202 | LTV-817S (TX) / LTV-817S (RX) | OPTO-SMD-4_L4.6-W6.5-P2.54-LS10.3-BL | [C109227](https://jlcpcb.com/partdetail/C109227) | Lite-On LTV-817S-TA1-C | Basic | 0.0790 | 0.16 |

## Not fitted (DNP)

| Reference | Value | Why it is on the board |
|---|---|---|

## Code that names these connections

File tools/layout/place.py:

"""Placement of the Andiron board by module area. Writes positions and the outline into tools/route/placed.kicad_pcb.

The board hangs on a wall with every field cable coming from below or from the left (geometry.py):
  bottom edge   OpenTherm terminal in the left corner, then the four relay channels: terminal on the edge with its
                entries facing out, relay above it lying on its side (coil left, NC/COM/NO right), driver above the coil
  left edge     Qwiic, USB-C, FLOW and OUTDOOR terminals, entries facing out
  top-left      ESP32-C6 module, antenna at the top edge (no cables there); its left pin column faces the left-edge
                connectors (I2C, EN, buttons, USB), its right column the spare header, BOOT, relay drives and OT_OUT
  below module  power: USB protection at the receptacle, bulk capacitor, regulator; 1-Wire parts at the probe terminals
  bottom-left   OpenTherm field side (fuse, TVS, bridge) next to its terminal; transistor stage and optos in a row
                above the drivers
  right of module  controls: I2C pull-ups, LEDs, buttons and their RC filters
  top-right     the OLED's Qwiic socket over an empty area; the module sits in the cover window on a short cable
usage: <kicad python> -I tools/layout/place.py <board>
"""
import sys, os, importlib.util, pcbnew
from pcbnew import FromMM, VECTOR2I
_spec = importlib.util.spec_from_file_location("geometry", os.path.join(os.path.dirname(os.path.abspath(__file__)), "geometry.py"))
G = importlib.util.module_from_spec(_spec); _spec.loader.exec_module(G)

B = sys.argv[1]; board = pcbnew.LoadBoard(B)
W, H = G.W, G.H
P = {}
def p(ref, x, y, rot=0): P[ref] = (x, y, rot)

# ---- relay strip along the bottom edge
for n, xr in enumerate(G.RX, start=1):
    p(f"K10{n}", xr, G.RY, 90)                   # rotation 90: coil pins left at xr-12.6, contacts NC/COM/NO to the right
    p(f"J11{n}", xr + G.TERM_CX, G.TERM_Y, 0)    # pin 1 NC, entries facing the bottom edge
    x0 = xr + G.COIL_DX                           # coil column; the driver sits above the coil
    p(f"Q10{n}", x0 - 1.5, 58.5, 0)
    p(f"R1{n}1", x0 - 1.5, 54.5, 0)              # 100 R gate
    p(f"R1{n}2", x0 - 1.5, 52.0, 0)              # 100 k pull-down
    p(f"D10{n}", x0 + 3.2, 58.5, 90)             # flyback
    p(f"LED10{n}", x0 + 6.0, 58.5, 90)
    p(f"R1{n}3", x0 + 6.0, 54.0, 270)            # LED resistor, +5V pad towards the rail

# ---- MCU: antenna end at the top edge. Pins: left column x U1-8.75, top to bottom 1 GND, 2 3V3, 3 EN, 4 BTN1, 5 BTN2,
# 6 SDA, 7 SCL, 8 1-Wire, 9 OT_IN, 10 STATUS, 11 IO10, 12 IO11, 13/14 USB; right column top to bottom 28 GND, 27 OT_OUT,
# 26 RLY4, 25 IO16, 24 IO17, 23 OT LED, 21-19 RLY3..1, 17 IO19, 16 IO18, 15 BOOT. Pin pitch 1.27, pin 1 at U1y-8.25.
UX, UY = 27.0, 16.3
p("U1", UX, UY, 0)
# C6/C7 at the 3V3 pin are placed below once the pin position is known
p("R4", 13.0, 13.5, 0); p("C8", 13.0, 16.0, 0)    # EN RC beside the EN pin
p("J7", 40.0, 10.0, 0)                            # spare GPIO header, vertical, along the right pin column
p("R5", 34.0, 28.2, 0)                            # BOOT pull-up, under the BOOT pin

# ---- left edge: Qwiic, USB-C, FLOW, OUTDOOR (all but J1 snapped to the edge below)
p("J6", 4.0, 13.0, 270)                           # Qwiic beside the I2C pins
p("J1", 4.5, 24.5, 270)                           # USB-C level with the module's USB pins; shell lip 0.3 mm from the edge
p("J3", 4.0, 36.0, 270); p("J4", 4.0, 49.0, 270)  # FLOW, OUTDOOR
p("R14", 16.0, 39.5, 90); p("R15", 16.0, 43.0, 90); p("D2", 16.0, 47.5, 90)  # 1-Wire pull-up, series R, TVS (x 8-14 left free for labels)

# ---- power, below the module
p("U3", 12.8, 24.5, 90)                           # USB ESD between the receptacle and the module's USB pins
p("R1", 12.5, 19.5, 90); p("R2", 12.5, 29.0, 90)  # CC pull-downs
p("C1", 15.5, 29.0, 90); p("R3", 15.5, 21.0, 90)  # shield RC
p("D1", 16.2, 33.0, 90)                           # VBUS TVS
p("C2", 24.0, 34.0, 0)                            # 470 uF bulk
p("C3", 31.0, 34.0, 90); p("U2", 37.0, 34.0, 0); p("C4", 43.5, 34.0, 90); p("C5", 43.5, 37.3, 0)

# ---- OpenTherm: field side next to the terminal, transistor stage and optos in a row above the drivers and the +5V rail (opto pads reach 5 mm from centre)
p("J201", 14.0, 89.0, 0)
p("F201", 11.5, 78.0, 90); p("D208", 6.0, 78.0, 90)
for ref, x in [("D201", 3.5), ("D202", 6.5), ("D203", 9.5), ("D204", 12.5)]: p(ref, x, 68.5, 90)
p("Q201", 20.0, 42.0, 0); p("R201", 24.5, 42.0, 90)
p("D206", 28.0, 42.0, 90); p("D205", 31.0, 42.0, 90); p("R202", 33.8, 42.0, 90)
p("R203", 36.3, 42.0, 90); p("D207", 39.3, 42.0, 90)
p("U201", 48.5, 42.0, 0); p("R204", 53.0, 39.0, 90); p("U202", 57.5, 42.0, 0); p("R205", 62.5, 42.0, 90)

# ---- controls, right of the module
p("J5", *G.OLED_CONN, 0)                          # OLED Qwiic socket, opening facing down into the OLED area
p("R12", 63.0, 10.0, 0); p("R13", 63.0, 12.5, 0)  # I2C pull-ups
p("LED1", 69.0, 9.0, 0); p("R8", 69.0, 11.5, 0); p("R9", 73.5, 9.0, 0)     # STATUS LED
p("LED2", 69.0, 14.5, 0); p("R10", 69.0, 17.0, 0); p("R11", 73.5, 14.5, 0)   # OT activity LED
for ref, x in [("SW1", 52.0), ("SW2", 59.5), ("SW3", 67.0), ("SW4", 74.5)]: p(ref, x, 22.5, 90)   # RESET BOOT BTN1 BTN2
p("R6", 59.0, 29.5, 0); p("C9", 59.0, 32.0, 0)    # BTN1 RC
p("R7", 66.0, 29.5, 0); p("C10", 66.0, 32.0, 0)   # BTN2 RC

# ---- mechanical
p("H1", 4.0, 4.0); p("H2", W - 4.0, 4.0); p("H3", 4.0, H - 4.0); p("H4", W - 4.0, H - 4.0)
p("FID1", 50.0, 4.0); p("FID2", W - 4.0, 48.0); p("FID3", 92.0, 47.0)

missing = []
for f in board.Footprints():
    r = f.GetReference()
    if r in ("C6", "C7"): continue
    if r not in P: missing.append(r); continue
    x, y, rot = P[r]
    f.SetOrientationDegrees(rot); f.SetPosition(VECTOR2I(FromMM(x), FromMM(y)))

# left-edge connectors: courtyard 0.5 mm from the edge (J1 is placed exactly, its shell lip at 0.3 mm)
for f in board.Footprints():
    r = f.GetReference()
    if r in G.EDGE_CONNECTORS and G.EDGE_CONNECTORS[r][0] == "left" and r != "J1":
        c = f.GetCourtyard(pcbnew.F_CrtYd); bb = c.BBox() if c.OutlineCount() else f.GetBoundingBox(False, False)
        f.Move(VECTOR2I(FromMM(0.5) - bb.GetLeft(), 0))

# decoupling at the module's 3V3 pin (pin 2): C7 in line with the pin, C6 beside it, both clear of the antenna keep-out
u1 = [f for f in board.Footprints() if f.GetReference() == "U1"][0]
p3 = [p_ for p_ in u1.Pads() if p_.GetNumber() == "2"][0].GetPosition()
x3, y3 = p3.x / 1e6, p3.y / 1e6
for f in board.Footprints():
    if f.GetReference() == "C7": f.SetOrientationDegrees(0); f.SetPosition(VECTOR2I(FromMM(x3 - 2.8), FromMM(y3)))
    if f.GetReference() == "C6": f.SetOrientationDegrees(90); f.SetPosition(VECTOR2I(FromMM(x3 - 5.75), FromMM(y3 + 0.2)))

# board outline
for d in list(board.GetDrawings()):
    if d.GetLayer() == pcbnew.Edge_Cuts: board.Remove(d)
sh = pcbnew.PCB_SHAPE(board); sh.SetShape(pcbnew.SHAPE_T_RECT); sh.SetLayer(pcbnew.Edge_Cuts)
sh.SetStart(VECTOR2I(0, 0)); sh.SetEnd(VECTOR2I(FromMM(W), FromMM(H))); sh.SetWidth(FromMM(0.1)); board.Add(sh)
pcbnew.SaveBoard(B, board)
print("placed", len(P) + 2, "| not placed:", missing or "none", f"| U1 3V3 pin at ({x3:.2f}, {y3:.2f})")
